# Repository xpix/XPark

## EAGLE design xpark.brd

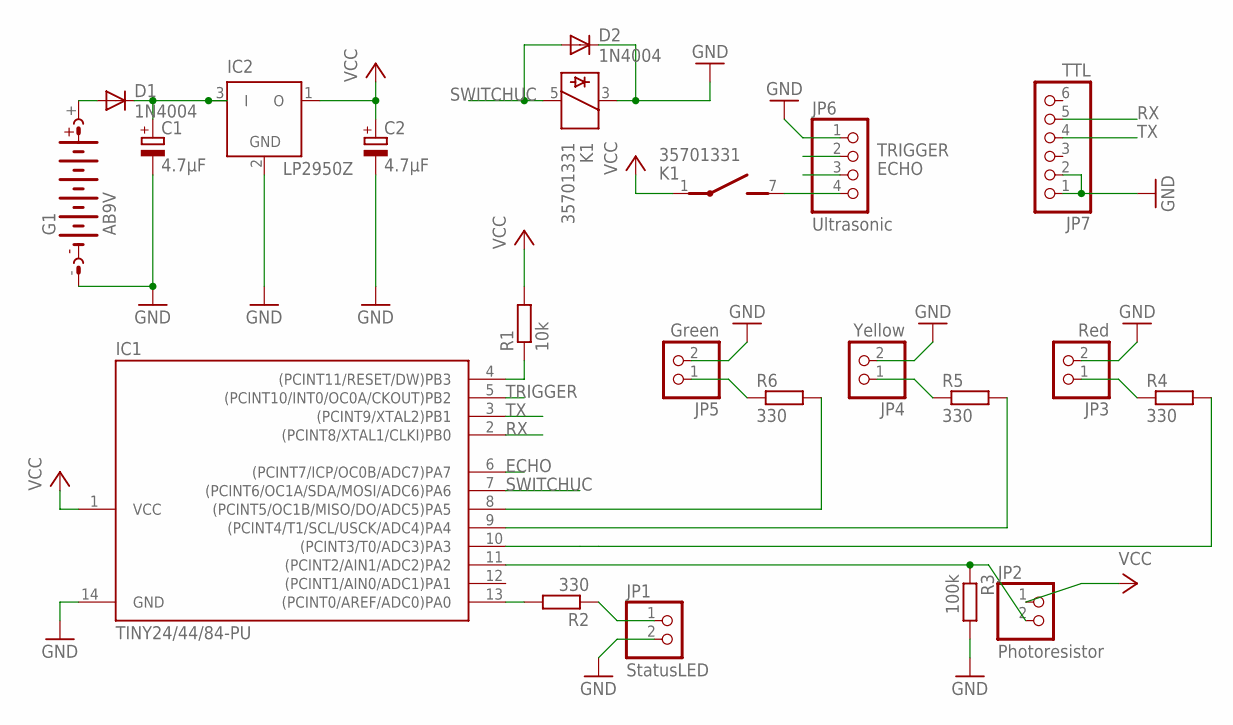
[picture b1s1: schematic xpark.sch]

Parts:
C1, C2: 4.7µF; E2,5-5
D1, D2: 1N4004; DO41-10
G1: AB9V
IC1: TINY24/44/84-PU; DIL14
IC2: LP2950Z; TO92
JP1: StatusLED; 1X02
JP2: Photoresistor; 1X02
JP3: Red; 1X02
JP4: Yellow; 1X02
JP5: Green; 1X02
JP6: Ultrasonic; 1X04
JP7: TTL; 1X06
K1: 35701331; REED
R1: 10k; 0204/7
R2, R4, R5, R6: 330; 0204/7
R3: 100k; 0204/7

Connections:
ECHO: IC1.6 ((PCINT7/ICP/OC0B/ADC7)PA7), JP6.3
GND: C1.-, C2.-, D2.C, G1.-, IC1.14 (GND), IC2.2 (GND), JP1.2, JP3.2, JP4.2, JP5.2, JP6.1, JP7.1, JP7.2, K1.3, R3.2
unnamed: IC1.11 ((PCINT2/AIN1/ADC2)PA2), JP2.2, R3.1
unnamed: IC1.4 ((PCINT11/RESET/DW)PB3), R1.1
unnamed: JP6.4, K1.7 (S)
unnamed: IC1.8 ((PCINT5/OC1B/MISO/DO/ADC5)PA5), R6.2
unnamed: D1.A, G1.+
unnamed: IC1.13 ((PCINT0/AREF/ADC0)PA0), R2.2
unnamed: IC1.9 ((PCINT4/T1/SCL/USCK/ADC4)PA4), R5.2
unnamed: IC1.10 ((PCINT3/T0/ADC3)PA3), R4.2
unnamed: C1.+, D1.C, IC2.3 (I)
RX: IC1.2 ((PCINT8/XTAL1/CLKI)PB0), JP7.5
STATUSLED: JP1.1, R2.1
STATUSLED1: JP3.1, R4.1
STATUSLED2: JP4.1, R5.1
STATUSLED3: JP5.1, R6.1
SWITCHUC: D2.A, IC1.7 ((PCINT6/OC1A/SDA/MOSI/ADC6)PA6), K1.5
TRIGGER: IC1.5 ((PCINT10/INT0/OC0A/CKOUT)PB2), JP6.2
TX: IC1.3 ((PCINT9/XTAL2)PB1), JP7.4
VCC: C2.+, IC1.1 (VCC), IC2.1 (O), JP2.1, K1.1, R1.2

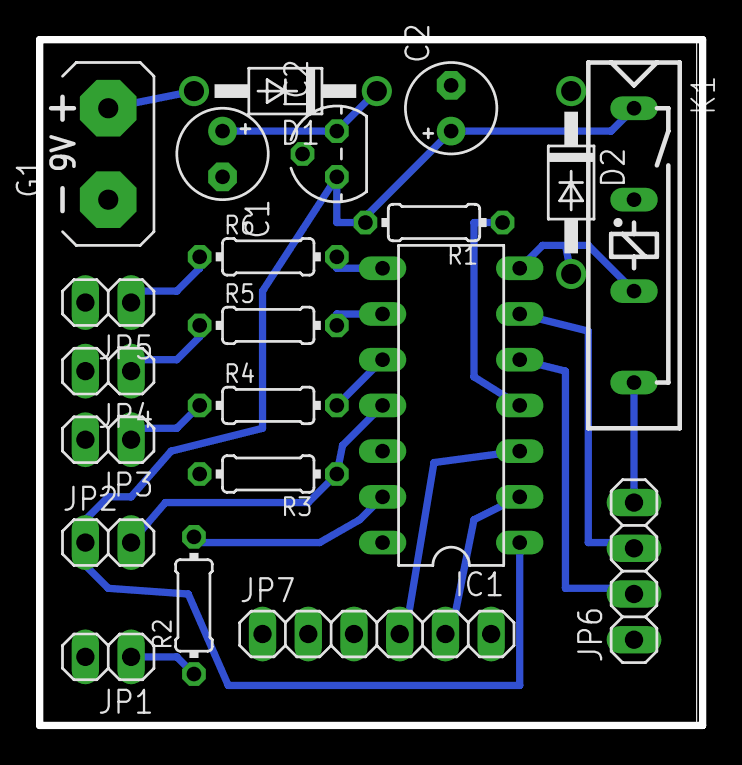
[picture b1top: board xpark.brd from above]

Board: 2 copper layers, 36.8 x 38.1 mm, 21 parts (0 on the bottom side), 20 nets.

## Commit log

2013-08-06 Publish finished Project XPARK to github
